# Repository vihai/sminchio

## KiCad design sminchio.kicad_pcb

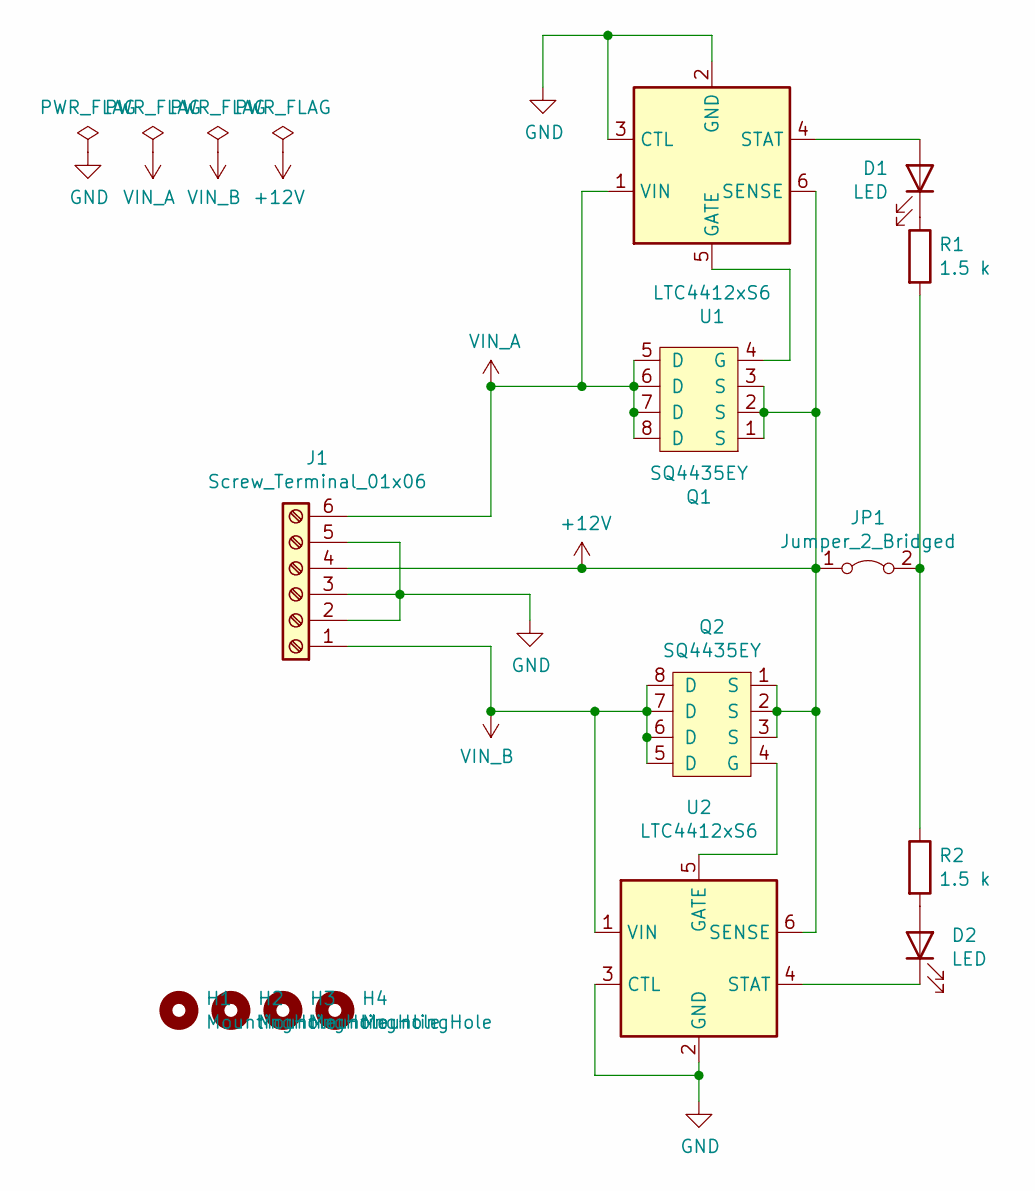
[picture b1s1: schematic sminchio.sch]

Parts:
D1, D2: LED; LED_0603
H1, H2, H3, H4: MountingHole; MountingHole_2.2mm_M2
J1: Screw_Terminal_01x06; PhoenixContact_MC-G_06x5.08mm_Angled
JP1: Jumper_2_Bridged; Pin_Header_Straight_1x02_Pitch2.54mm
Q1, Q2: SQ4435EY; SO-8
R1, R2: 1.5 k; R_0603
U1, U2: LTC4412xS6; TSOT-23-6

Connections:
+12V: J1.4, JP1.1 (A), Q1.1 (S), Q1.2 (S), Q1.3 (S), Q2.1 (S), Q2.2 (S), Q2.3 (S), U1.6 (SENSE), U2.6 (SENSE)
GND: J1.2, J1.3, J1.5, U1.2 (GND), U1.3 (CTL), U2.2 (GND), U2.3 (CTL)
unnamed: D1.1 (K), R1.1
unnamed: D1.2 (A), U1.4 (STAT)
unnamed: D2.1 (K), U2.4 (STAT)
unnamed: D2.2 (A), R2.2
unnamed: JP1.2 (B), R1.2, R2.1
unnamed: Q1.4 (G), U1.5 (GATE)
unnamed: Q2.4 (G), U2.5 (GATE)
VIN_A: J1.6, Q1.5 (D), Q1.6 (D), Q1.7 (D), Q1.8 (D), U1.1 (VIN)
VIN_B: J1.1, Q2.5 (D), Q2.6 (D), Q2.7 (D), Q2.8 (D), U2.1 (VIN)

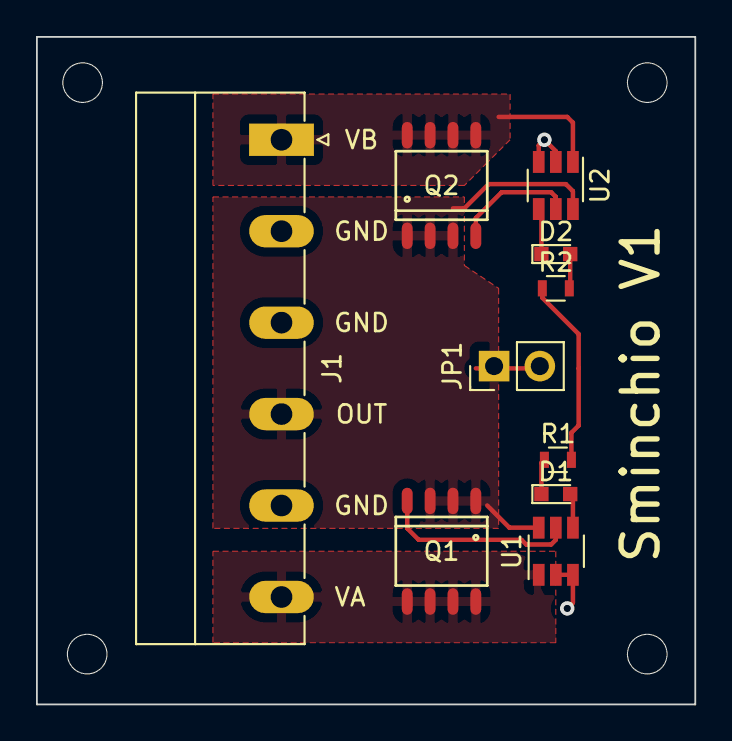
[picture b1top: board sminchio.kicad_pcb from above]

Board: 2 copper layers, 36.6 x 37.1 mm, 14 parts (0 on the bottom side), 11 nets.

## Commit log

2021-06-07 Almost complete version
